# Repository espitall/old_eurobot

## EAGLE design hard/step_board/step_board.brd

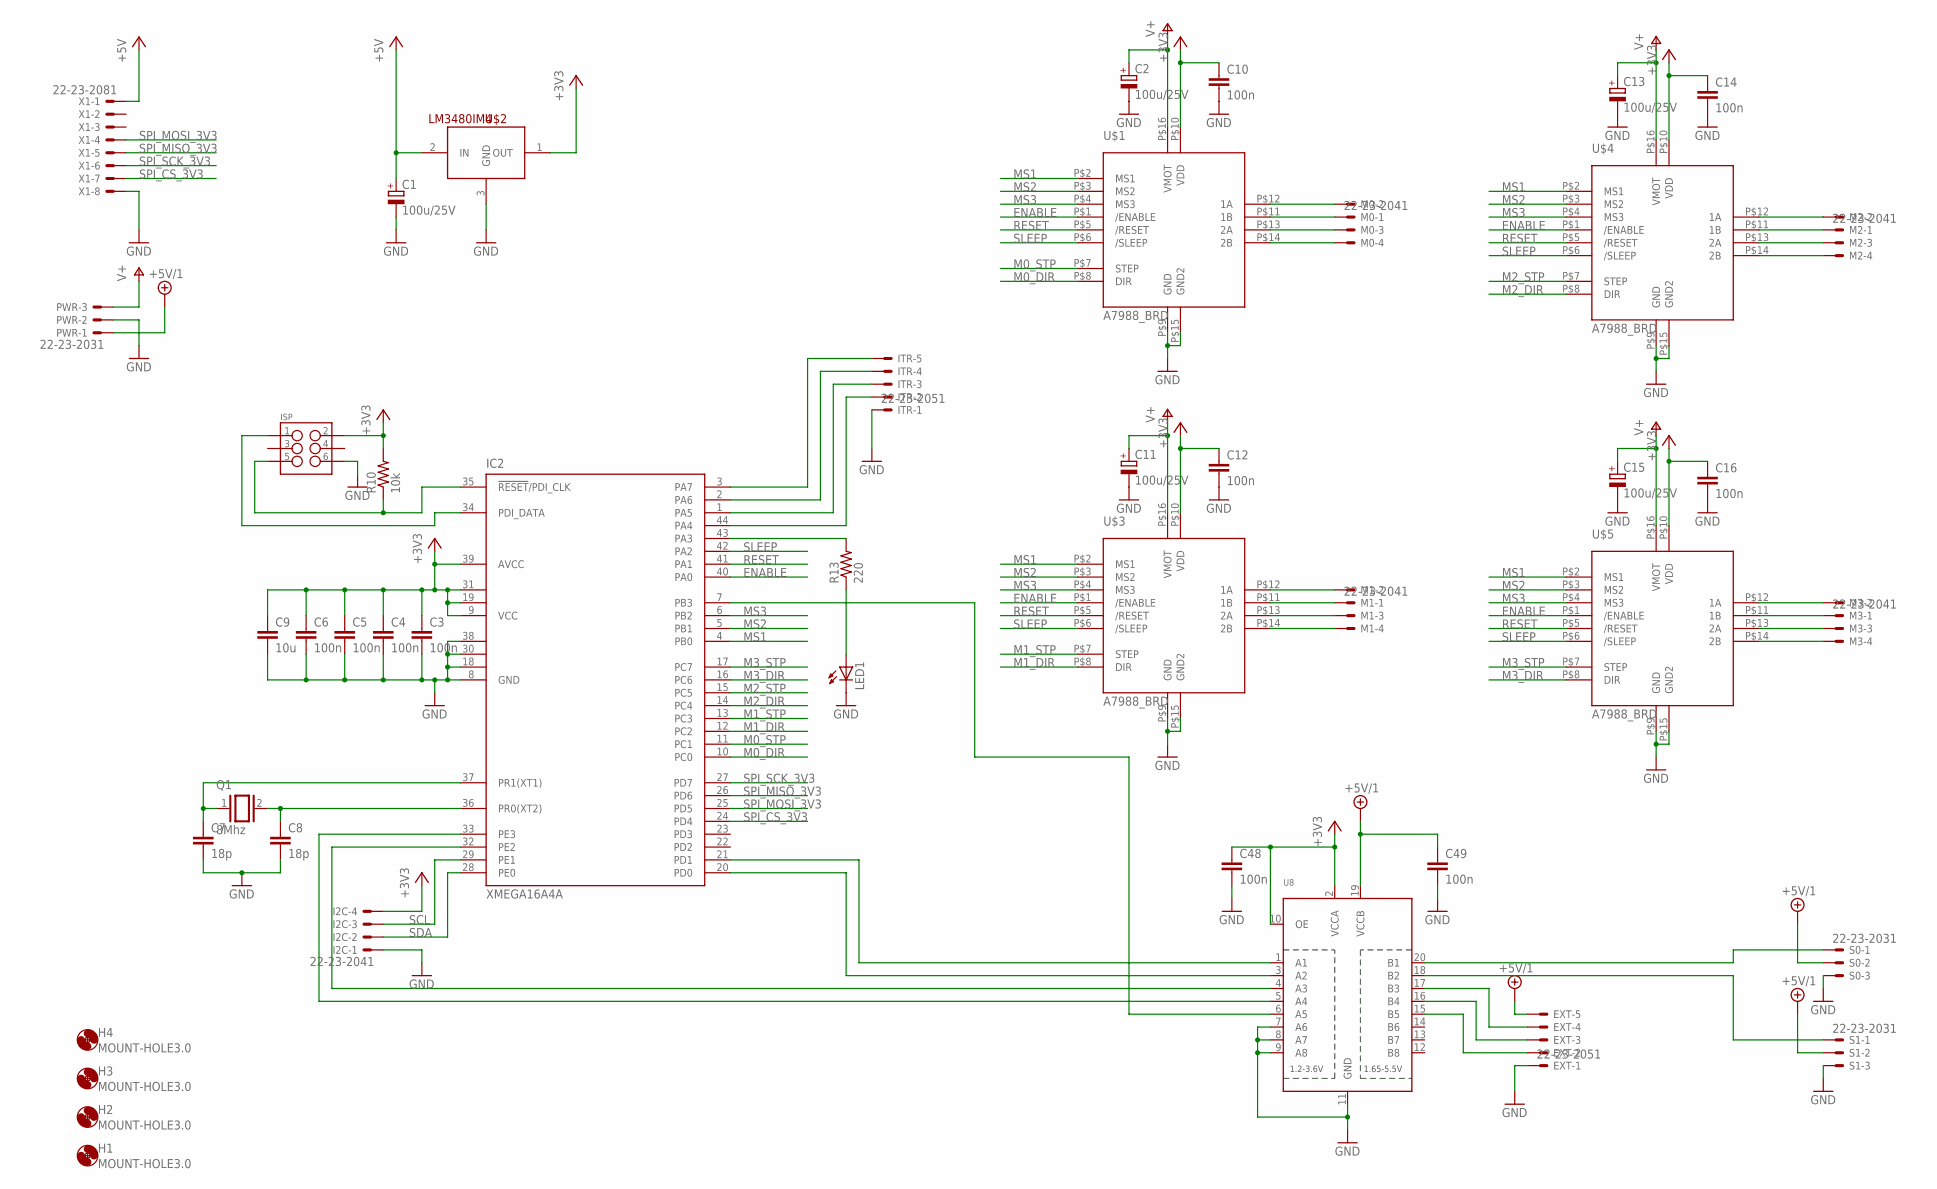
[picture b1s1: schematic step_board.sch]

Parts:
C1, C2, C11, C13, C15: 100u/25V; PANASONIC_E
C3, C4, C5, C6, C10, C12, C14, C16: 100n; C0603
C7, C8: 18p; C0603
C9: 10u; C0805
C48, C49: 100n; C0603K
EXT: 22-23-2051
H1, H2, H3, H4: MOUNT-HOLE3.0; 3,0
I2C: 22-23-2041
IC2: XMEGA16A4A; TQFP44
ISP: M03X2POGO_PINS; 2X3_POGO
ITR: 22-23-2051
LED1: LEDCHIP-LED0603; CHIP-LED0603
M0, M1, M2, M3: 22-23-2041
PWR: 22-23-2031
Q1: 8Mhz; QS
R10: 10k; R0603
R13: 220; R0603
S0, S1: 22-23-2031
U8: TXB0108PWR; TSSOP20
U$1, U$3, U$4, U$5: A7988_BRD; A4988_BRD
U$2: LM3480IM4; SOT23-3
X1: 22-23-2081

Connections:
+3V3: C3.1, C4.1, C5.1, C6.1, C9.1, C10.1, C12.1, C14.1, C16.1, C48.1, I2C.4, IC2.9 (VCC), IC2.19 (VCC1), IC2.31 (VCC2), IC2.39 (AVCC), ISP.P$2 (2), R10.2, U8.2 (VCCA), U8.10 (OE), U$1.P$10 (VDD), U$2.1 (OUT), U$3.P$10 (VDD), U$4.P$10 (VDD), U$5.P$10 (VDD)
+5V: C1.+, U$2.2 (IN), X1.1
+5V/1: C49.1, EXT.5, PWR.1, S0.2, S1.2, U8.19 (VCCB)
ENABLE: IC2.40 (PA0), U$1.P$1 (/ENABLE), U$3.P$1 (/ENABLE), U$4.P$1 (/ENABLE), U$5.P$1 (/ENABLE)
GND: C1.-, C2.-, C3.2, C4.2, C5.2, C6.2, C7.2, C8.2, C9.2, C10.2, C11.-, C12.2, C13.-, C14.2, C15.-, C16.2, C48.2, C49.2, EXT.1, I2C.1, IC2.8 (GND), IC2.18 (GND1), IC2.30 (GND2), IC2.38 (GND3), ISP.P$6 (6), ITR.1, LED1.C, PWR.2, S0.3, S1.3, U8.7 (A6), U8.8 (A7), U8.9 (A8), U8.11 (GND), U$1.P$9 (GND), U$1.P$15 (GND2), U$2.3 (GND), U$3.P$9 (GND), U$3.P$15 (GND2), U$4.P$9 (GND), U$4.P$15 (GND2), U$5.P$9 (GND), U$5.P$15 (GND2), X1.8
M0_DIR: IC2.10 (PC0), U$1.P$8 (DIR)
M0_STP: IC2.11 (PC1), U$1.P$7 (STEP)
M1_DIR: IC2.12 (PC2), U$3.P$8 (DIR)
M1_STP: IC2.13 (PC3), U$3.P$7 (STEP)
M2_DIR: IC2.14 (PC4), U$4.P$8 (DIR)
M2_STP: IC2.15 (PC5), U$4.P$7 (STEP)
M3_DIR: IC2.16 (PC6), U$5.P$8 (DIR)
M3_STP: IC2.17 (PC7), U$5.P$7 (STEP)
MS1: IC2.4 (PB0), U$1.P$2 (MS1), U$3.P$2 (MS1), U$4.P$2 (MS1), U$5.P$2 (MS1)
MS2: IC2.5 (PB1), U$1.P$3 (MS2), U$3.P$3 (MS2), U$4.P$3 (MS2), U$5.P$3 (MS2)
MS3: IC2.6 (PB2), U$1.P$4 (MS3), U$3.P$4 (MS3), U$4.P$4 (MS3), U$5.P$4 (MS3)
unnamed: M0.1, U$1.P$11 (1B)
unnamed: M0.2, U$1.P$12 (1A)
unnamed: M2.1, U$4.P$11 (1B)
unnamed: LED1.A, R13.1
unnamed: IC2.34 (PDI_DATA), ISP.P$1 (1)
unnamed: C8.1, IC2.36 (PR0(XT2)), Q1.2
unnamed: C7.1, IC2.37 (PR1(XT1)), Q1.1
unnamed: M2.2, U$4.P$12 (1A)
unnamed: M0.3, U$1.P$13 (2A)
unnamed: IC2.35 (!RESET!/PDI_CLK), ISP.P$5 (5), R10.1
unnamed: M0.4, U$1.P$14 (2B)
unnamed: IC2.43 (PA3), R13.2
unnamed: M1.3, U$3.P$13 (2A)
unnamed: M1.4, U$3.P$14 (2B)
unnamed: M1.1, U$3.P$11 (1B)
unnamed: M1.2, U$3.P$12 (1A)
unnamed: M2.3, U$4.P$13 (2A)
unnamed: M2.4, U$4.P$14 (2B)
unnamed: M3.1, U$5.P$11 (1B)
unnamed: M3.2, U$5.P$12 (1A)
unnamed: M3.3, U$5.P$13 (2A)
unnamed: M3.4, U$5.P$14 (2B)
unnamed: S0.1, U8.20 (B1)
unnamed: IC2.20 (PD0), U8.3 (A2)
unnamed: IC2.21 (PD1), U8.1 (A1)
unnamed: S1.1, U8.18 (B2)
unnamed: IC2.32 (PE2), U8.4 (A3)
unnamed: IC2.33 (PE3), U8.5 (A4)
unnamed: IC2.44 (PA4), ITR.2
unnamed: EXT.4, U8.17 (B3)
unnamed: EXT.3, U8.16 (B4)
unnamed: EXT.2, U8.15 (B5)
unnamed: IC2.1 (PA5), ITR.3
unnamed: IC2.2 (PA6), ITR.4
unnamed: IC2.3 (PA7), ITR.5
unnamed: IC2.7 (PB3), U8.6 (A5)
RESET: IC2.41 (PA1), U$1.P$5 (/RESET), U$3.P$5 (/RESET), U$4.P$5 (/RESET), U$5.P$5 (/RESET)
SCL: I2C.3, IC2.29 (PE1)
SDA: I2C.2, IC2.28 (PE0)
SLEEP: IC2.42 (PA2), U$1.P$6 (/SLEEP), U$3.P$6 (/SLEEP), U$4.P$6 (/SLEEP), U$5.P$6 (/SLEEP)
SPI_CS_3V3: IC2.24 (PD4), X1.7
SPI_MISO_3V3: IC2.26 (PD6), X1.5
SPI_MOSI_3V3: IC2.25 (PD5), X1.4
SPI_SCK_3V3: IC2.27 (PD7), X1.6
V+: C2.+, C11.+, C13.+, C15.+, PWR.3, U$1.P$16 (VMOT), U$3.P$16 (VMOT), U$4.P$16 (VMOT), U$5.P$16 (VMOT)

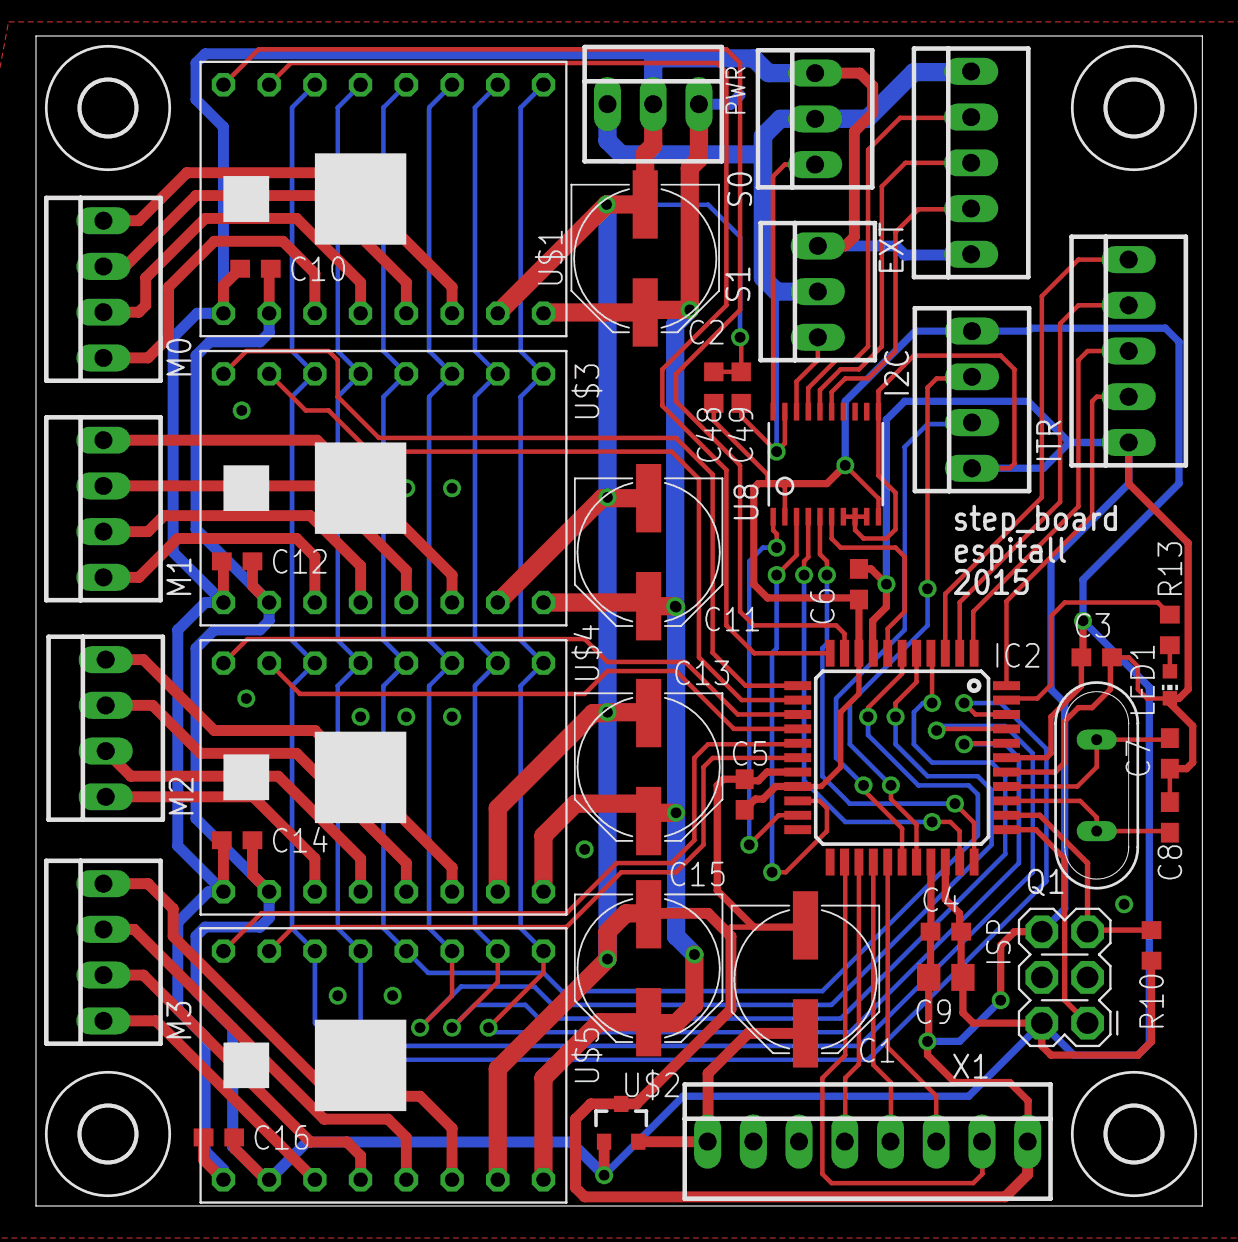
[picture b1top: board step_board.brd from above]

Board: 2 copper layers, 64.8 x 65.0 mm, 45 parts (0 on the bottom side), 61 nets.

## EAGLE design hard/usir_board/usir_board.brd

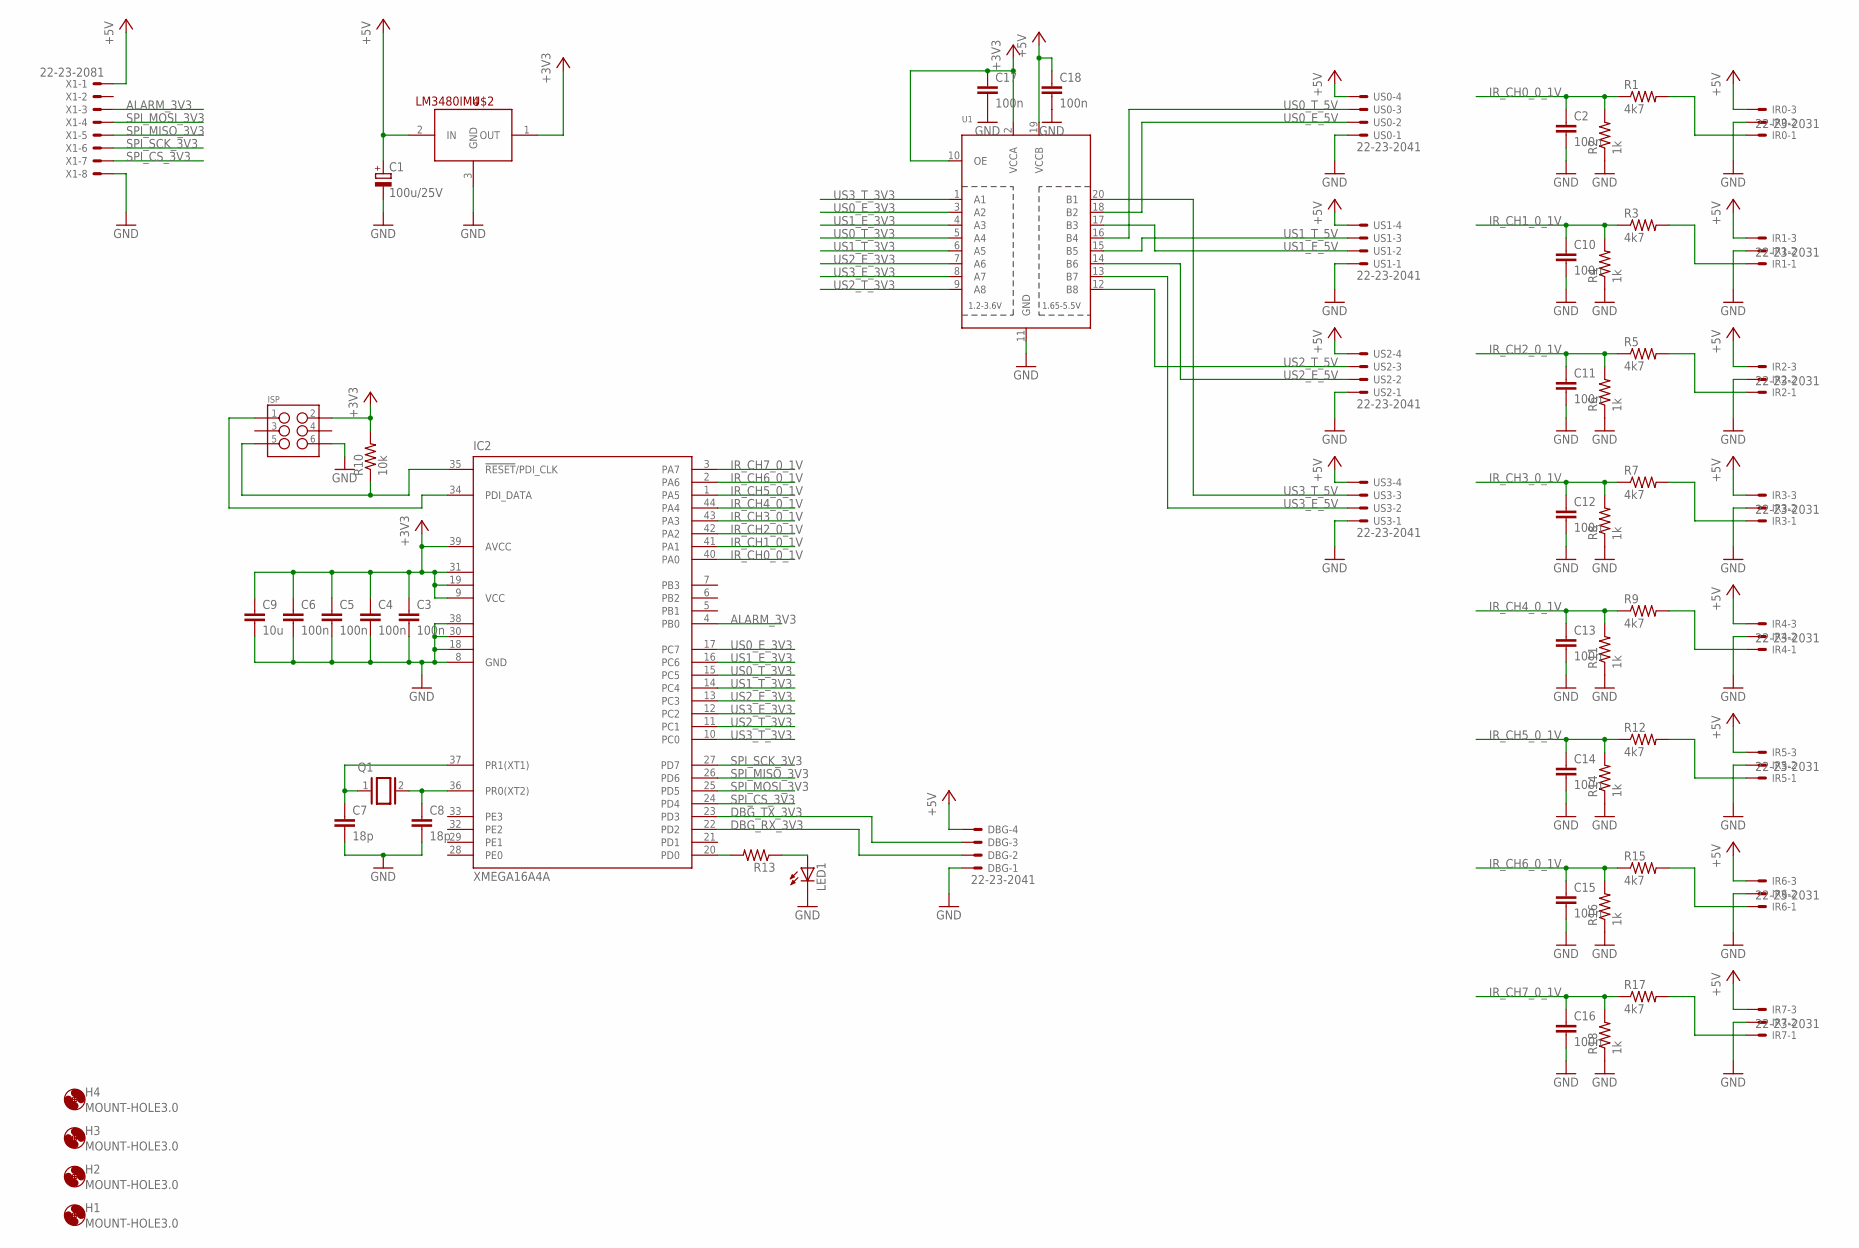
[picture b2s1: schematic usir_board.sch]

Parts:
C1: 100u/25V; PANASONIC_E
C2, C3, C4, C5, C6, C10, C11, C12, C13, C14, C15, C16, C17, C18: 100n; C0603
C7, C8: 18p; C0603
C9: 10u; C0805
DBG: 22-23-2041
H1, H2, H3, H4: MOUNT-HOLE3.0; 3,0
IC2: XMEGA16A4A; TQFP44
IR0, IR1, IR2, IR3, IR4, IR5, IR6, IR7: 22-23-2031
ISP: M03X2POGO_PINS; 2X3_POGO
LED1: LEDCHIP-LED0603; CHIP-LED0603
Q1: XTAL/S; QS
R1, R3, R5, R7, R9, R12, R15, R17: 4k7; R0603
R2, R4, R6, R8, R11, R14, R16, R18: 1k; R0603
R10: 10k; R0603
R13: R-US_R0603; R0603
U1: TXB0108PWR; TSSOP20
U$2: LM3480IM4; SOT23-3
US0, US1, US2, US3: 22-23-2041
X1: 22-23-2081

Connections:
+3V3: C3.1, C4.1, C5.1, C6.1, C9.1, C17.1, IC2.9 (VCC), IC2.19 (VCC1), IC2.31 (VCC2), IC2.39 (AVCC), ISP.P$2 (2), R10.2, U1.2 (VCCA), U1.10 (OE), U$2.1 (OUT)
+5V: C1.+, C18.1, DBG.4, IR0.3, IR1.3, IR2.3, IR3.3, IR4.3, IR5.3, IR6.3, IR7.3, U1.19 (VCCB), U$2.2 (IN), US0.4, US1.4, US2.4, US3.4, X1.1
ALARM_3V3: IC2.4 (PB0), X1.3
DBG_RX_3V3: DBG.2, IC2.22 (PD2)
DBG_TX_3V3: DBG.3, IC2.23 (PD3)
GND: C1.-, C2.2, C3.2, C4.2, C5.2, C6.2, C7.2, C8.2, C9.2, C10.2, C11.2, C12.2, C13.2, C14.2, C15.2, C16.2, C17.2, C18.2, DBG.1, IC2.8 (GND), IC2.18 (GND1), IC2.30 (GND2), IC2.38 (GND3), IR0.2, IR1.2, IR2.2, IR3.2, IR4.2, IR5.2, IR6.2, IR7.2, ISP.P$6 (6), LED1.C, R2.1, R4.1, R6.1, R8.1, R11.1, R14.1, R16.1, R18.1, U1.11 (GND), U$2.3 (GND), US0.1, US1.1, US2.1, US3.1, X1.8
IR_CH0_0_1V: C2.1, IC2.40 (PA0), R1.1, R2.2
IR_CH1_0_1V: C10.1, IC2.41 (PA1), R3.1, R4.2
IR_CH2_0_1V: C11.1, IC2.42 (PA2), R5.1, R6.2
IR_CH3_0_1V: C12.1, IC2.43 (PA3), R7.1, R8.2
IR_CH4_0_1V: C13.1, IC2.44 (PA4), R9.1, R11.2
IR_CH5_0_1V: C14.1, IC2.1 (PA5), R12.1, R14.2
IR_CH6_0_1V: C15.1, IC2.2 (PA6), R15.1, R16.2
IR_CH7_0_1V: C16.1, IC2.3 (PA7), R17.1, R18.2
unnamed: IR1.1, R3.2
unnamed: IR0.1, R1.2
unnamed: IR2.1, R5.2
unnamed: LED1.A, R13.1
unnamed: IC2.34 (PDI_DATA), ISP.P$1 (1)
unnamed: C8.1, IC2.36 (PR0(XT2)), Q1.2
unnamed: C7.1, IC2.37 (PR1(XT1)), Q1.1
unnamed: IR3.1, R7.2
unnamed: IR4.1, R9.2
unnamed: IC2.35 (!RESET!/PDI_CLK), ISP.P$5 (5), R10.1
unnamed: IR5.1, R12.2
unnamed: IC2.20 (PD0), R13.2
unnamed: IR6.1, R15.2
unnamed: IR7.1, R17.2
SPI_CS_3V3: IC2.24 (PD4), X1.7
SPI_MISO_3V3: IC2.26 (PD6), X1.5
SPI_MOSI_3V3: IC2.25 (PD5), X1.4
SPI_SCK_3V3: IC2.27 (PD7), X1.6
US0_E_3V3: IC2.17 (PC7), U1.3 (A2)
US0_E_5V: U1.18 (B2), US0.2
US0_T_3V3: IC2.15 (PC5), U1.5 (A4)
US0_T_5V: U1.16 (B4), US0.3
US1_E_3V3: IC2.16 (PC6), U1.4 (A3)
US1_E_5V: U1.17 (B3), US1.2
US1_T_3V3: IC2.14 (PC4), U1.6 (A5)
US1_T_5V: U1.15 (B5), US1.3
US2_E_3V3: IC2.13 (PC3), U1.7 (A6)
US2_E_5V: U1.14 (B6), US2.2
US2_T_3V3: IC2.11 (PC1), U1.9 (A8)
US2_T_5V: U1.12 (B8), US2.3
US3_E_3V3: IC2.12 (PC2), U1.8 (A7)
US3_E_5V: U1.13 (B7), US3.2
US3_T_3V3: IC2.10 (PC0), U1.1 (A1)
US3_T_5V: U1.20 (B1), US3.3

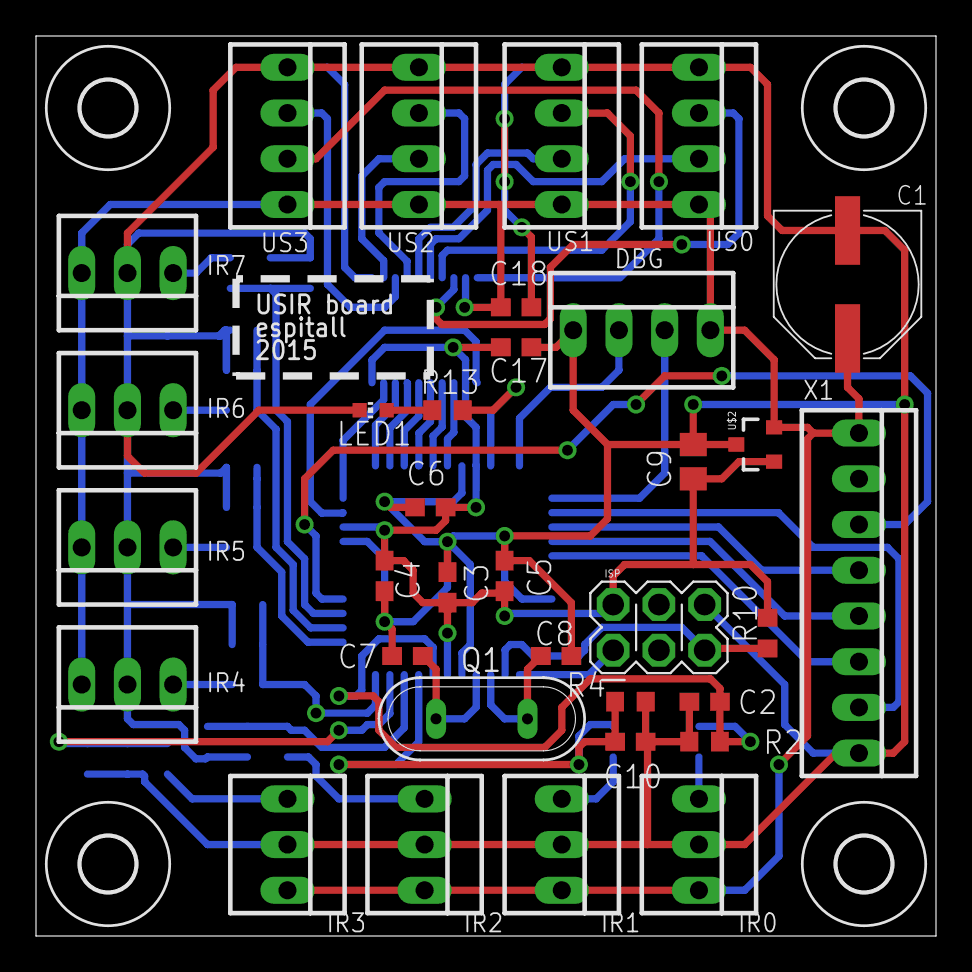
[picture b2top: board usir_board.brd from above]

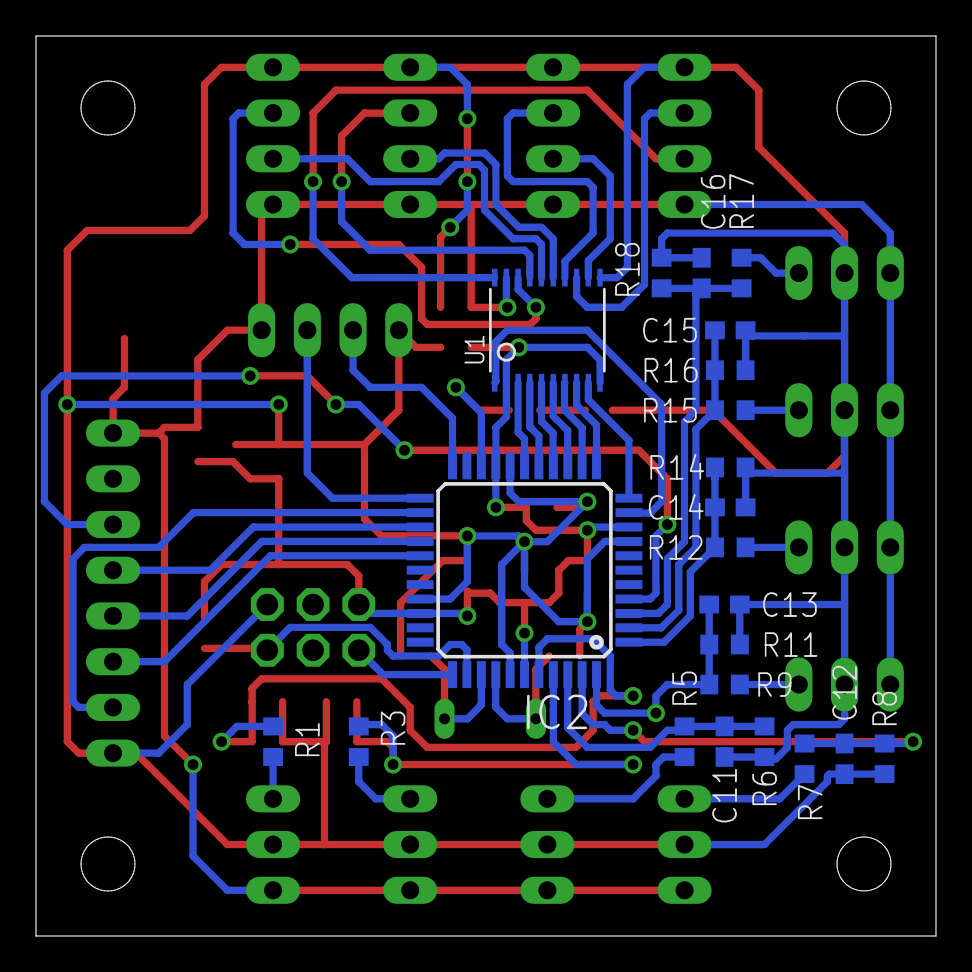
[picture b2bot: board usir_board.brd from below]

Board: 2 copper layers, 50.0 x 50.0 mm, 60 parts (22 on the bottom side), 48 nets.

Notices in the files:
parts and their libraries:
SparkFun-DigitalIC: Licensing: Creative Commons ShareAlike 4.0 International - https://creativecommons.org/licenses/by-sa/4.0
